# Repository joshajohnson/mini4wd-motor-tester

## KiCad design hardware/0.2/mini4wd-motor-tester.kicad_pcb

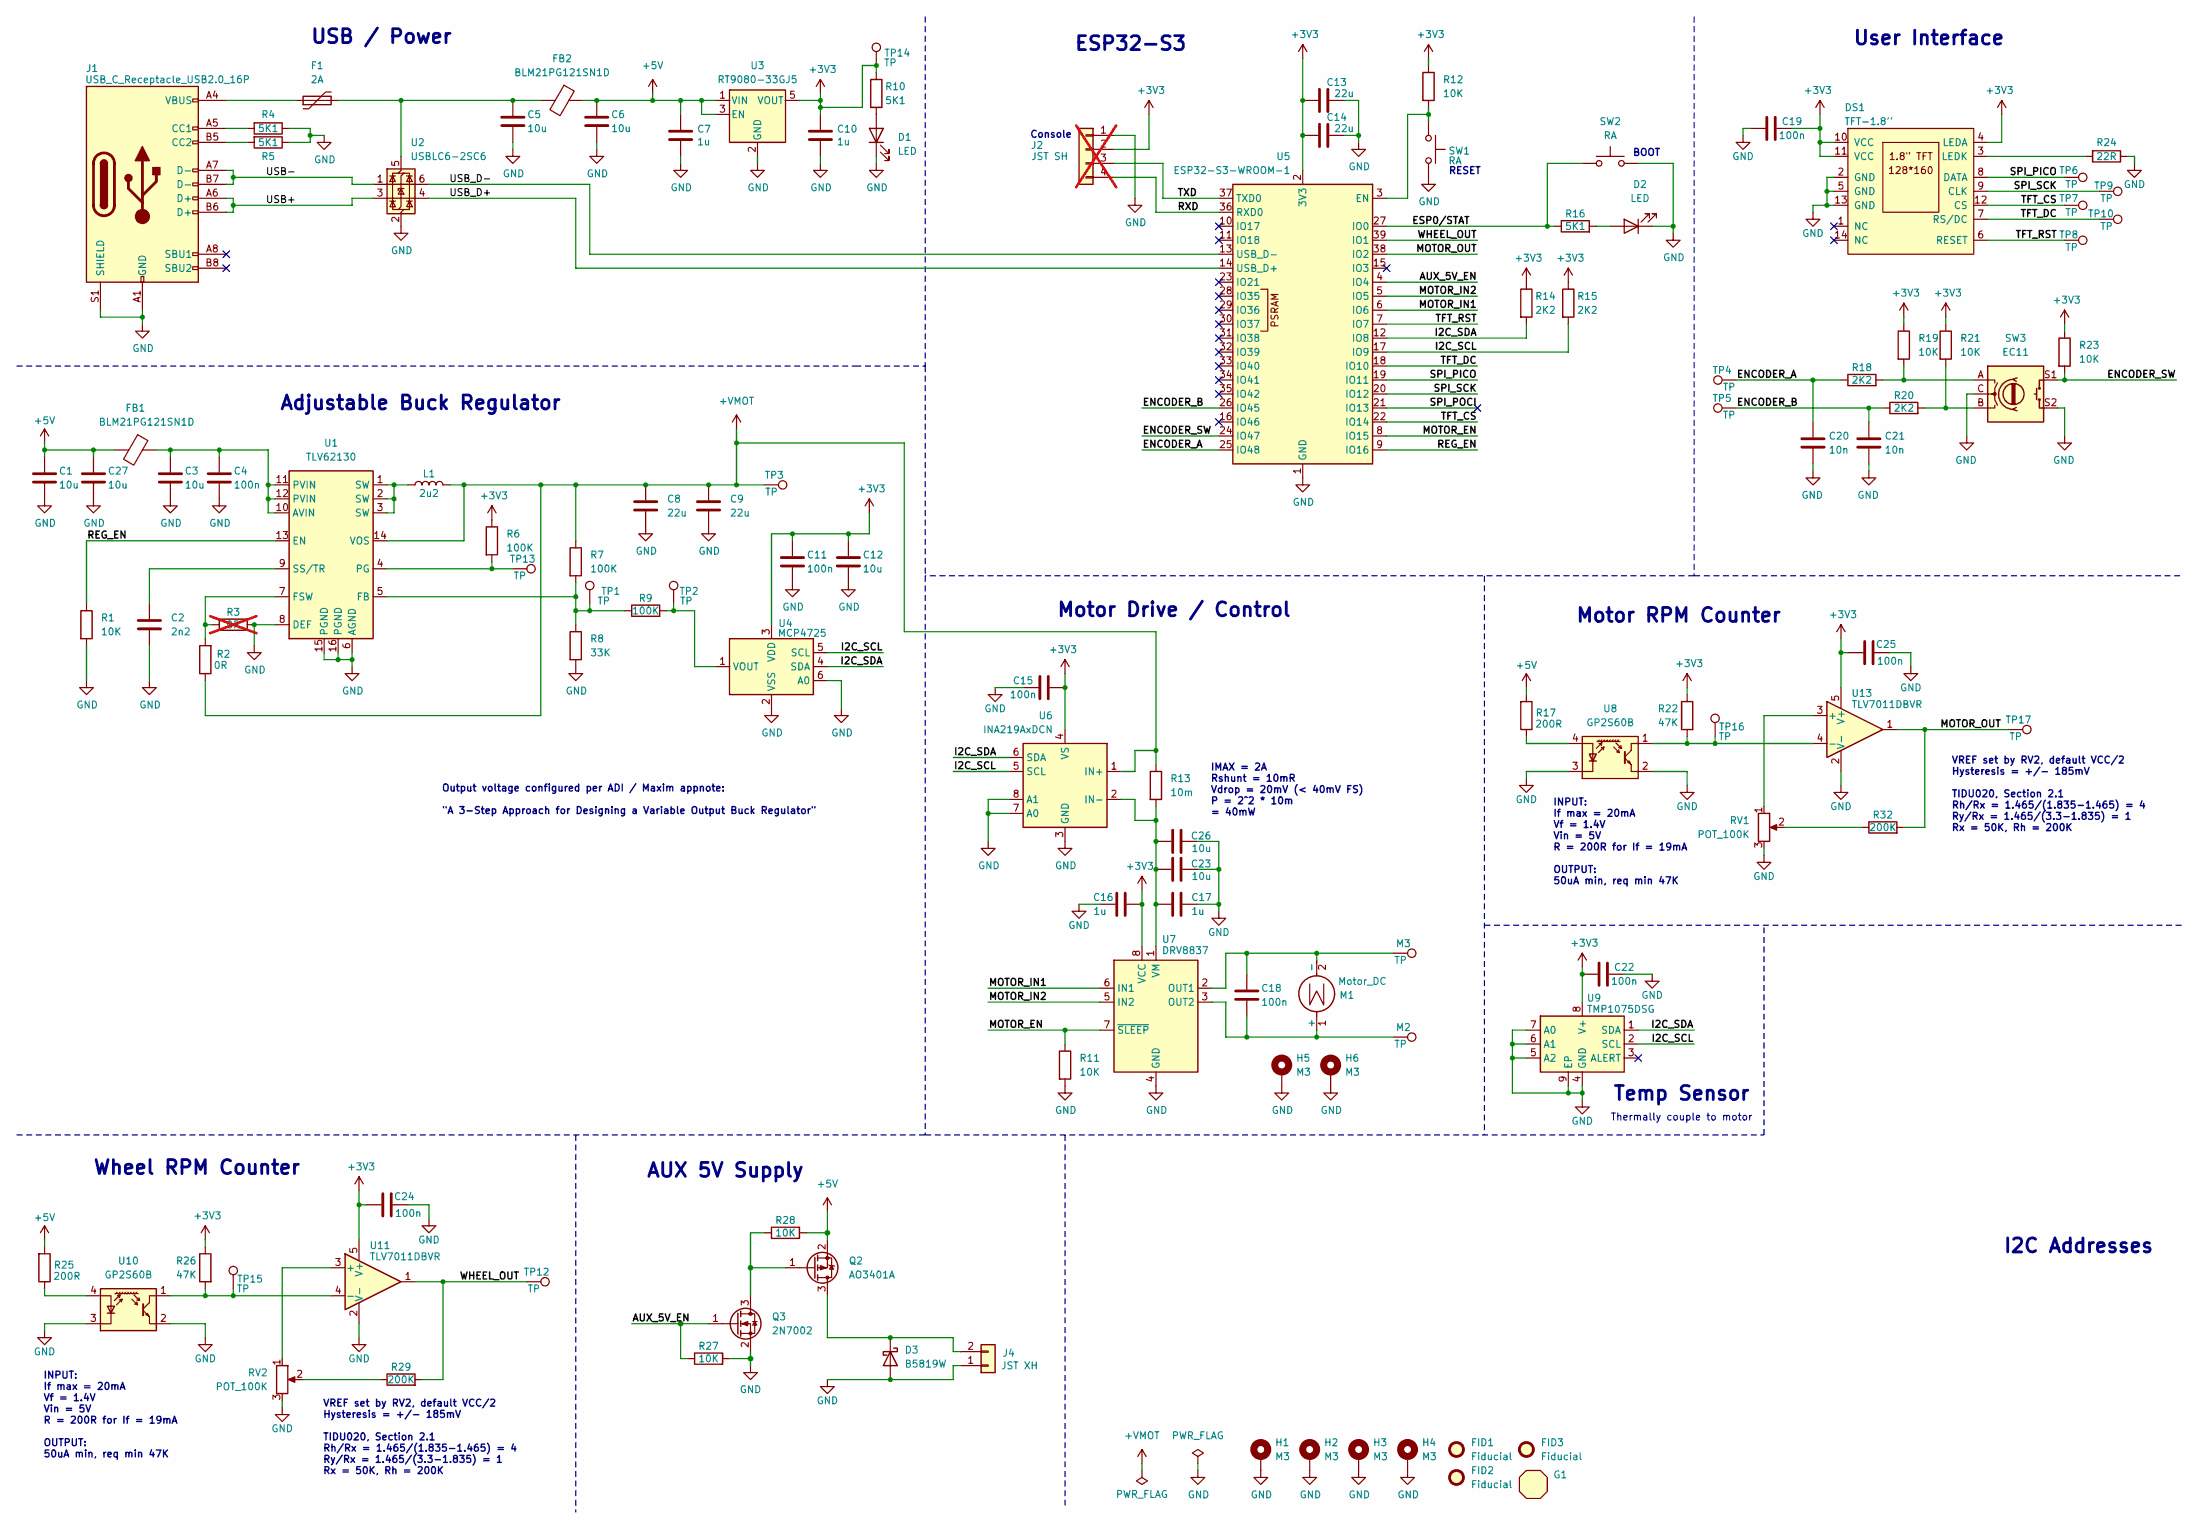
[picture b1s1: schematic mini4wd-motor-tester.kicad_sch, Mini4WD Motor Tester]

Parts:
C1, C3, C5, C6, C12, C23, C26, C27: 10u; C_0805_2012Metric; MPN GRM21BR61H106KE43L; LCSC C440198
C2: 2n2; C_0603_1608Metric; MPN 0603B222K500NT; LCSC C1604
C4, C11, C15, C18, C19, C22, C24, C25: 100n; C_0603_1608Metric; MPN CC0603KRX7R9BB104; LCSC C14663
C7, C10, C16, C17: 1u; C_0603_1608Metric; MPN CL10A105KB8NNNC; LCSC C15849
C8, C9, C13, C14: 22u; C_1206_3216Metric; MPN CL31A226KAHNNNE; LCSC C12891
C20, C21: 10n; C_0603_1608Metric; MPN 0603B103K500NT; LCSC C57112
D1, D2: LED; LED_0603_1608Metric; MPN KT-0603R; LCSC C2286
D3: B5819W; D_SOD-123; MPN B5819W SL; LCSC C8598
DS1: TFT-1.8''; 1.8TFT; MPN N177-1216TCWPG01-H14; LCSC C5123575
F1: 2A; Fuse_1206_3216Metric; MPN NANOSMDC200F-2; LCSC C2153712
FB1, FB2: BLM21PG121SN1D; L_0805_2012Metric; MPN BLM21PG121SN1D; LCSC C79382
FID1, FID2, FID3: Fiducial; Fiducial_1mm_Mask3mm
G1: josh-details
H1, H2, H3, H4, H5, H6: M3; MountingHole_3.2mm_M3_DIN965_Pad_TopBottom
J1: USB_C_Receptacle_USB2.0_16P; USB_C_Receptacle_HRO_TYPE-C-31-M-12; MPN TYPE-C-31-M-12; LCSC C165948
J2: JST SH; JST_SH_SM04B-SRSS-TB_1x04-1MP_P1.00mm_Horizontal; MPN SM04B-SRSS-TB(LF)(SN); LCSC C160404; not fitted
J4: JST XH; JST_XH_S2B-XH-A_1x02_P2.50mm_Horizontal; MPN S2B-XH-A(LF)(SN); LCSC C157931
L1: 2u2; L_Vishay_IHLP-1616; MPN PSPMAA0402-2R2M-ANP; LCSC C436515
M1: Motor_DC; Mini4WD_Motor
M2, M3: TP; TestPoint_THTPad_D1.5mm_Drill0.7mm
Q2: AO3401A; SOT-23; MPN AO3401A; LCSC C15127
Q3: 2N7002; SOT-23; MPN 2N7002; LCSC C8545
R1, R11, R12, R19, R21, R23, R27, R28: 10K; R_0603_1608Metric; MPN 0603WAF1002T5E; LCSC C25804
R2: 0R; R_0603_1608Metric; MPN 0603WAF0000T5E; LCSC C21189
R3: 0R; R_0603_1608Metric; MPN 0603WAF0000T5E; LCSC C21189; not fitted
R4, R5, R10, R16: 5K1; R_0603_1608Metric; MPN 0603WAF5101T5E; LCSC C23186
R6, R7, R9: 100K; R_0603_1608Metric; MPN 0603WAF1003T5E; LCSC C25803
R8: 33K; R_0603_1608Metric; MPN 0603WAF3302T5E; LCSC C4216
R13: 10m; R_1206_3216Metric; MPN CSR1206FT10L0; LCSC C346769
R14, R15, R18, R20: 2K2; R_0603_1608Metric; MPN 0603WAF2201T5E; LCSC C4190
R17, R25: 200R; R_0603_1608Metric; MPN 0603WAF2000T5E; LCSC C8218
R22, R26: 47K; R_0603_1608Metric; MPN 0603WAF4702T5E; LCSC C25819
R24: 22R; R_0603_1608Metric; MPN 0603WAF220JT5E; LCSC C23345
R29, R32: 200K; R_0603_1608Metric; MPN 0603WAF2003T5E; LCSC C25811
RV1, RV2: POT_100K; Potentiometer_Bourns_TC33X_Vertical; MPN TC33X-2-104E; LCSC C719186
SW1, SW2: RA; SW_PUSH_EVQPUL_EVQPUC; MPN TS-1186D-C-A; LCSC C397351
SW3: EC11; RotaryEncoder_Alps_EC11E_15MM; MPN PEC11R-4215F-S0024; LCSC C143790
TP1, TP2, TP3, TP4, TP5, TP6, TP7, TP8, TP9, TP10, TP12, TP13, TP14, TP15, TP16, TP17: TP; TestPoint_Pad_D1.0mm
U1: TLV62130; VQFN-16-1EP_3x3mm_P0.5mm_EP1.68x1.68mm; MPN TLV62130RGTR; LCSC C122479
U2: USBLC6-2SC6; SOT-23-6; MPN USBLC6-2SC6; LCSC C7519
U3: RT9080-33GJ5; SOT-23-5; MPN RT9080-33GJ5; LCSC C841192
U4: MCP4725; SOT-23-6; MPN MCP4725A0T-E/CH; LCSC C144198
U5: ESP32-S3-WROOM-1; MPN ESP32-S3-WROOM-1-N16R2; LCSC C2913205
U6: INA219AxDCN; SOT-23-8; MPN INA219AIDCNR; LCSC C87469
U7: DRV8837; WSON-8-1EP_2x2mm_P0.5mm_EP0.9x1.6mm; MPN DRV8837DSGR; LCSC C39159
U8, U10: GP2S60B; Sharp_GP2S60B; MPN GP2S60B; LCSC C83485
U9: TMP1075DSG; WSON-8-1EP_2x2mm_P0.5mm_EP0.9x1.6mm; MPN TMP1075DSGR; LCSC C2870250
U11, U13: TLV7011DBVR; SOT-23-5; MPN TLV7011DBVR; LCSC C702117

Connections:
+3V3: C10.2, C11.1, C12.1, C13.2, C14.2, C15.2, C16.1, C19.1, C22.2, C24.1, C25.1, DS1.4 (LEDA), DS1.10 (VCC), DS1.11 (VCC), J2.2, R6.1, R10.1, R12.1, R14.1, R15.1, R19.1, R21.1, R22.1, R23.1, R26.1, TP14.1, U3.5 (VOUT), U4.3 (VDD), U5.2 (3V3), U6.4 (VS), U7.8 (VCC), U9.8 (V+), U11.5 (V+), U13.5 (V+)
+5V: C1.1, C6.1, C7.2, C27.1, FB1.2, FB2.1, Q2.2 (S), R17.2, R25.2, R28.2, U3.1 (VIN), U3.3 (EN)
+VMOT: C8.1, C9.1, L1.2, R2.1, R7.1, R13.1, TP3.1, U1.14 (VOS), U6.1 (IN+)
/AUX_5V_EN: Q3.1 (G), R27.1, U5.4 (IO4)
/ENCODER_A: C20.1, R18.1, TP4.1, U5.25 (IO48)
/ENCODER_B: C21.1, R20.1, TP5.1, U5.26 (IO45)
/ENCODER_SW: R23.2, SW3.S1, U5.24 (IO47)
/ESP0/STAT: R16.1, SW2.1, U5.27 (IO0)
/I2C_SCL: R15.2, U4.5 (SCL), U5.17 (IO9), U6.5 (SCL), U9.2 (SCL)
/I2C_SDA: R14.2, U4.4 (SDA), U5.12 (IO8), U6.6 (SDA), U9.1 (SDA)
/MOTOR_EN: R11.1, U5.8 (IO15), U7.7 (~SLEEP)
/MOTOR_IN1: U5.6 (IO6), U7.6 (IN1)
/MOTOR_IN2: U5.5 (IO5), U7.5 (IN2)
/MOTOR_OUT: R32.2, TP17.1, U5.38 (IO2), U13.1
/REG_EN: R1.1, U1.13 (EN), U5.9 (IO16)
/RXD: J2.4, U5.36 (RXD0)
/SPI_PICO: DS1.8 (DATA), TP6.1, U5.19 (IO11)
/SPI_POCI: U5.21 (IO13)
/SPI_SCK: DS1.9 (CLK), TP9.1, U5.20 (IO12)
/TFT_CS: DS1.12 (CS), TP7.1, U5.22 (IO14)
/TFT_DC: DS1.7 (RS/DC), TP10.1, U5.18 (IO10)
/TFT_RST: DS1.6 (RESET), TP8.1, U5.7 (IO7)
/TXD: J2.3, U5.37 (TXD0)
/USB+: J1.A6 (D+), J1.B6 (D+), U2.3 (I/O2)
/USB-: J1.A7 (D-), J1.B7 (D-), U2.1 (I/O1)
/USB_D+: U2.4 (I/O2), U5.14 (USB_D+)
/USB_D-: U2.6 (I/O1), U5.13 (USB_D-)
/WHEEL_OUT: R29.2, TP12.1, U5.39 (IO1), U11.1
GND: C1.2, C2.2, C3.2, C4.2, C5.2, C6.2, C7.1, C8.2, C9.2, C10.1, C11.2, C12.2, C13.1, C14.1, C15.1, C16.2, C17.2, C19.2, C20.2, C21.2, C22.1, C23.2, C24.2, C25.2, C26.2, C27.2, D1.1 (K), D2.1 (K), D3.2 (A), DS1.2 (GND), DS1.5 (GND), DS1.13 (GND), H1.1, H2.1, H3.1, H4.1, H5.1, H6.1, J1.A1 (GND), J1.A12 (GND), J1.B1 (GND), J1.B12 (GND), J1.S1 (SHIELD), J2.1, J4.1, Q3.2 (S), R1.2, R3.2, R4.1, R5.1, R8.2, R11.2, R24.1, R27.2, RV1.3, RV2.3, SW1.2, SW2.2, SW3.C, SW3.S2, U1.6 (AGND), U1.8 (DEF), U1.15 (PGND), U1.16 (PGND), U1.17 (AGND), U2.2 (GND), U3.2 (GND), U4.2 (VSS), U4.6 (A0), U5.1 (GND), U5.40 (GND), U5.41 (GND), U6.3 (GND), U6.7 (A0), U6.8 (A1), U7.4 (GND), U7.9 (GND), U8.2, U8.3 (K), U9.4 (GND), U9.5 (A2), U9.6 (A1), U9.7 (A0), U9.9 (EP), U10.2, U10.3 (K), U11.2 (V-), U13.2 (V-)
unnamed: D1.2 (A), R10.2
unnamed: D2.2 (A), R16.2
unnamed: D3.1 (K), J4.2, Q2.3 (D)
unnamed: DS1.3 (LEDK), R24.2
unnamed: F1.1, J1.A4 (VBUS), J1.A9 (VBUS), J1.B4 (VBUS), J1.B9 (VBUS)
unnamed: J1.A5 (CC1), R4.2
unnamed: J1.B5 (CC2), R5.2
unnamed: L1.1, U1.1 (SW), U1.2 (SW), U1.3 (SW)
unnamed: C18.2, M1.1 (+), M2.1, U7.3 (OUT2)
unnamed: C18.1, M1.2 (-), M3.1, U7.2 (OUT1)
unnamed: Q2.1 (G), Q3.3 (D), R28.1
unnamed: R18.2, R19.2, SW3.A
unnamed: R20.2, R21.2, SW3.B
unnamed: R29.1, RV2.2
unnamed: R32.1, RV1.2
unnamed: C3.1, C4.1, FB1.1, U1.10 (AVIN), U1.11 (PVIN), U1.12 (PVIN)
unnamed: R7.2, R8.1, R9.1, TP1.1, U1.5 (FB)
unnamed: R2.2, R3.1, U1.7 (FSW)
unnamed: R6.2, TP13.1, U1.4 (PG)
unnamed: C2.1, U1.9 (SS/TR)
unnamed: C5.1, F1.2, FB2.2, U2.5 (VBUS)
unnamed: R9.2, TP2.1, U4.1 (VOUT)
unnamed: R12.2, SW1.1, U5.3 (EN)
unnamed: C17.1, C23.1, C26.1, R13.2, U6.2 (IN-), U7.1 (VM)
unnamed: R17.1, U8.4 (A)
unnamed: R25.1, U10.4 (A)
unnamed: RV2.1, U11.3 (+)
unnamed: R26.2, TP15.1, U10.1, U11.4 (-)
unnamed: RV1.1, U13.3 (+)
unnamed: R22.2, TP16.1, U8.1, U13.4 (-)

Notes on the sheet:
Thermally couple to motor
Console
Temp Sensor
BOOT
Wheel RPM Counter
AUX 5V Supply
Motor RPM Counter
Adjustable Buck Regulator
User Interface
RESET
USB / Power
I2C Addresses
Motor Drive / Control
ESP32-S3
VREF set by RV2, default VCC/2 Hysteresis = +/- 185mV TIDU020, Section 2.1 Rh/Rx = 1.465/(1.835-1.465) = 4 Ry/Rx = 1.465/(3.3-1.835) = 1 Rx = 50K, Rh = 200K
INPUT: If max = 20mA Vf = 1.4V Vin = 5V R = 200R for If = 19mA OUTPUT: 50uA min, req min 47K
Output voltage configured per ADI / Maxim appnote: "A 3-Step Approach for Designing a Variable Output Buck Regulator"
IMAX = 2A Rshunt = 10mR Vdrop = 20mV (< 40mV FS) P = 2^2 * 10m = 40mW

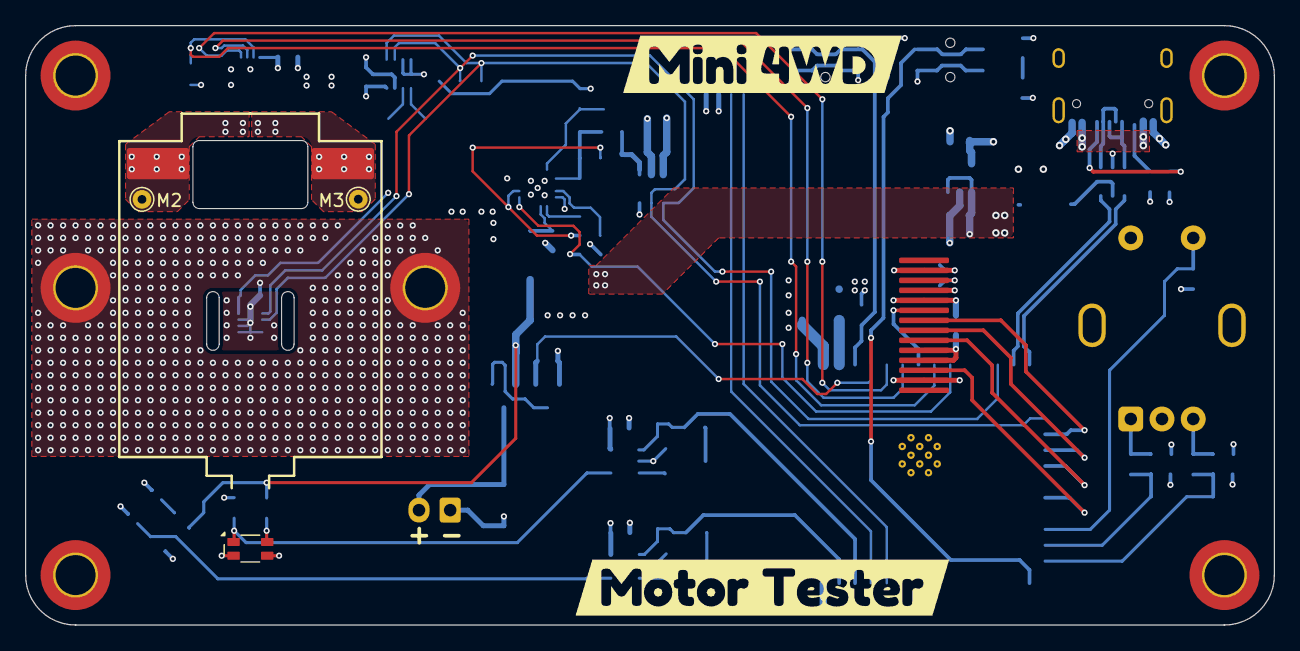
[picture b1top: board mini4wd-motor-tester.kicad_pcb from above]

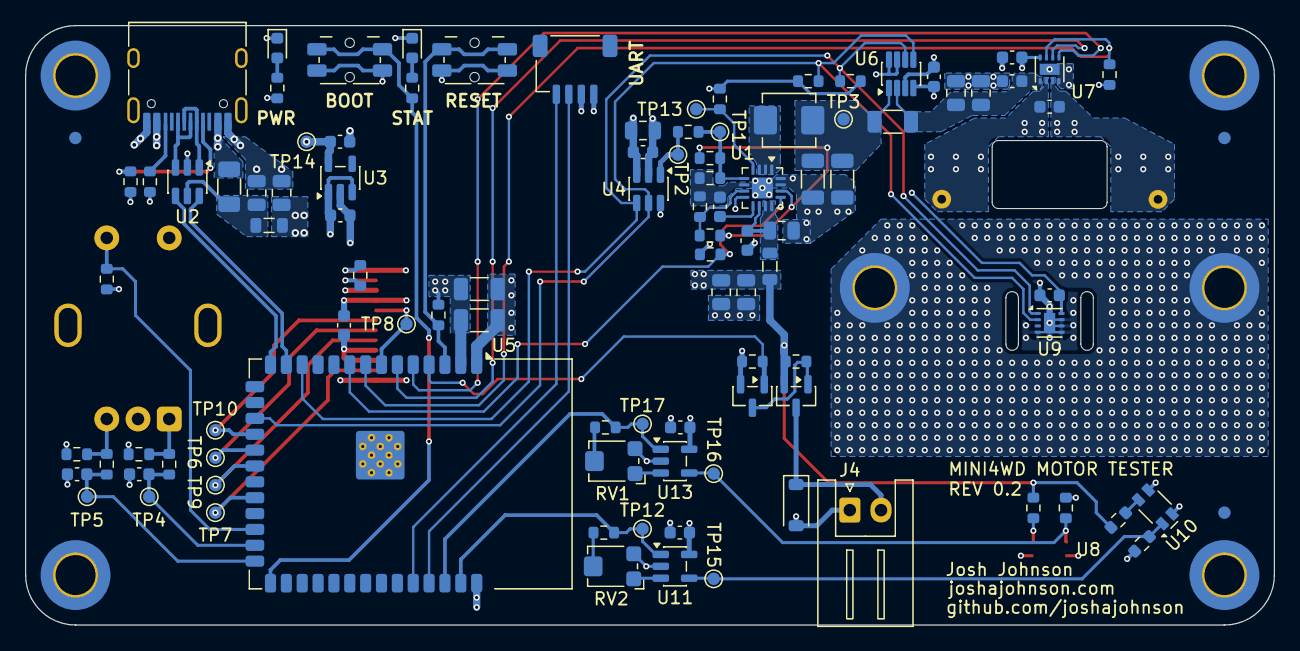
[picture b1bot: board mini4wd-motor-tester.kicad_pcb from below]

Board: 4 copper layers, 100.0 x 48.0 mm, 118 parts (104 on the bottom side), 58 nets.

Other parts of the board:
kibuzzard-697CCA76: G***; kibuzzard-697CCA76
kibuzzard-697CCA92: G***; kibuzzard-697CCA92

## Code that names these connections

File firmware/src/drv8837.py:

from machine import Pin


class DRV8837:
    """
    Control logic for DRV8837 motor driver.
    Does not support PWM speed control, only direction and brake.

    Example:

        motor = DRV8837(motor_en=15, motor_in1=6, motor_in2=5)
        motor.enable()
        motor.forward()
        motor.reverse()
        motor.brake()
        motor.disable()

    Datasheet: https://www.ti.com/lit/ds/symlink/drv8837.pdf

    """

    def __init__(
        self, motor_en: int = None, motor_in1: int = None, motor_in2: int = None
    ):
        self.motor_en = Pin(motor_en, Pin.OUT, Pin.PULL_DOWN)
        self.motor_in1 = Pin(motor_in1, Pin.OUT, Pin.PULL_DOWN)
        self.motor_in2 = Pin(motor_in2, Pin.OUT, Pin.PULL_DOWN)

    def enable(self):
        """Wake motor from sleep"""
        self.motor_en.value(1)

    def disable(self):
        """Put motor to sleep"""
        self.motor_en.value(0)

    def forward(self):
        """Set motor direction forward"""
        self.motor_in1.value(1)
        self.motor_in2.value(0)

    def reverse(self):
        """Set motor direction reverse"""
        self.motor_in1.value(0)
        self.motor_in2.value(1)

    def brake(self):
        """Brake motor"""
        self.motor_in1.value(0)
        self.motor_in2.value(0)

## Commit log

2026-01-27 initial commit after importing old template project
2026-01-27 sch done, all parts in pcb
2026-01-27 rough component placement
2026-01-27 add wheel rpm, aux 5V circuits
2026-01-27 update motor cutout, provision space for wheel speed tester
2026-01-28 shrinking board down
2026-01-28 rough placement of all parts on smaller board
2026-01-28 I think the final form has been reached?
2026-01-28 move encoder passives in from the edge
2026-01-28 cutouts under the motor
2026-01-30 change opto, move motor lower
2026-01-31 board passing erc and drc
2026-02-01 off to fab
2026-02-25 add 0.1 heatsink files
2026-02-25 add output files
2026-02-25 add gitignore
2026-02-25 add micropython + lvgl binary, test code, beginning of app code
2026-02-25 add temp sensor driver, update main to i2c detect then loop update temp
2026-02-25 improve tmp1075 driver, change i2cdetect formatting
2026-02-26 add ina219, mcp4725 drivers, write psu functions, check and calibrate dac / imon loop
2026-02-27 add rotary encoder, button, motor control. refactor lvgl display code. delete test code folder
2026-02-28 add averaging to current monitor, remove coast from motor control
2026-03-07 add motor state change logic, voltage ramping, average current measurement
2026-04-03 major updates, all working except regression in display init
2026-04-26 fix footprints
2026-04-26 wip r0.2
2026-05-03 add v2 heatsink, improve layout for v2 main
2026-05-03 minor sch and pcb updates
2026-06-08 begin UI dev - thanks Ant!
2026-06-08 moving globals out of the ui class
2026-06-12 home page and manual screen looking good
2026-06-12 linter go brrr
2026-06-12 remove unused back functions
2026-06-12 add placeholders for break-in, speed test, and settings
2026-06-12 improve pulse counter and UI
2026-06-12 split out gui, move to mv, finish manual page
2026-06-12 add speed screen, could do with better numbers tho
2026-06-12 tagging alpha, ready for race weekend
2026-06-12 set saves menu cursor position upon return, better manual default values
